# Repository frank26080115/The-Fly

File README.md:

# The-Fly

This device is a Bluetooth meeting audio recording device. It can record meetings, phone calls, or voice memos. During the recording, the user can also use this device to participate in the meeting, as it features a speaker, a earphone jack, and internal microphone.

The audio recordings are stored on a microSD card.

It features Wi-Fi connectivity so that AI can be used to transcribe and summarize the audio recordings. A local network PC can run scripts that run local AI models that performs the transcription and summarization.

## User Manuals

 * [Main Device](user-docs/user-manual-main-device.md)
 * [Wi-Fi Operations](user-docs/user-manual-wifi-operations.md)
 * [Local Server](user-docs/user-manual-local-server.md)

## Technical Breakdown

The device is a [M5Stack Core2](https://docs.m5stack.com/en/core/core2). It features a ESP32-D0WDQ6-V3 as the main microcontroller. This microcontroller features Bluetooth Classic and Wi-Fi connectivity.

There is a colour LCD screen with a capacitive touch panel, used to implement the GUI. The GUI is structured for quick usage, with shortcuts to your favorite Bluetooth host devices and the ability to instantly start a memo recording.

The Fly connects to any Bluetooth host, such as a smartphone or a laptop, using the "hands free profile", meaning it pretends to be a early 2010s era earphone and microphone, which gives it nearly universal compatibility with all host devices and all host software. No need to install any dedicated software, and it is practically impossible to detect or block.

Wi-Fi operation is implemented so the user can download and transcribe the recorded audio files. The process can be automated to any level the user desires. All the software can be completely local and private.

To improve audio quality, I've also created a daughterboard for the M5Stack Core2 that uses a SGTL5000 codec and provides a earphone jack along with a better internal mic, plus it supports inline mics on the earbuds.

(note: the original internal speaker and internal mic of the M5Stack Core2 have terrible audio quality)

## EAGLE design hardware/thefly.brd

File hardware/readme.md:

circuit designs and mechanical designs

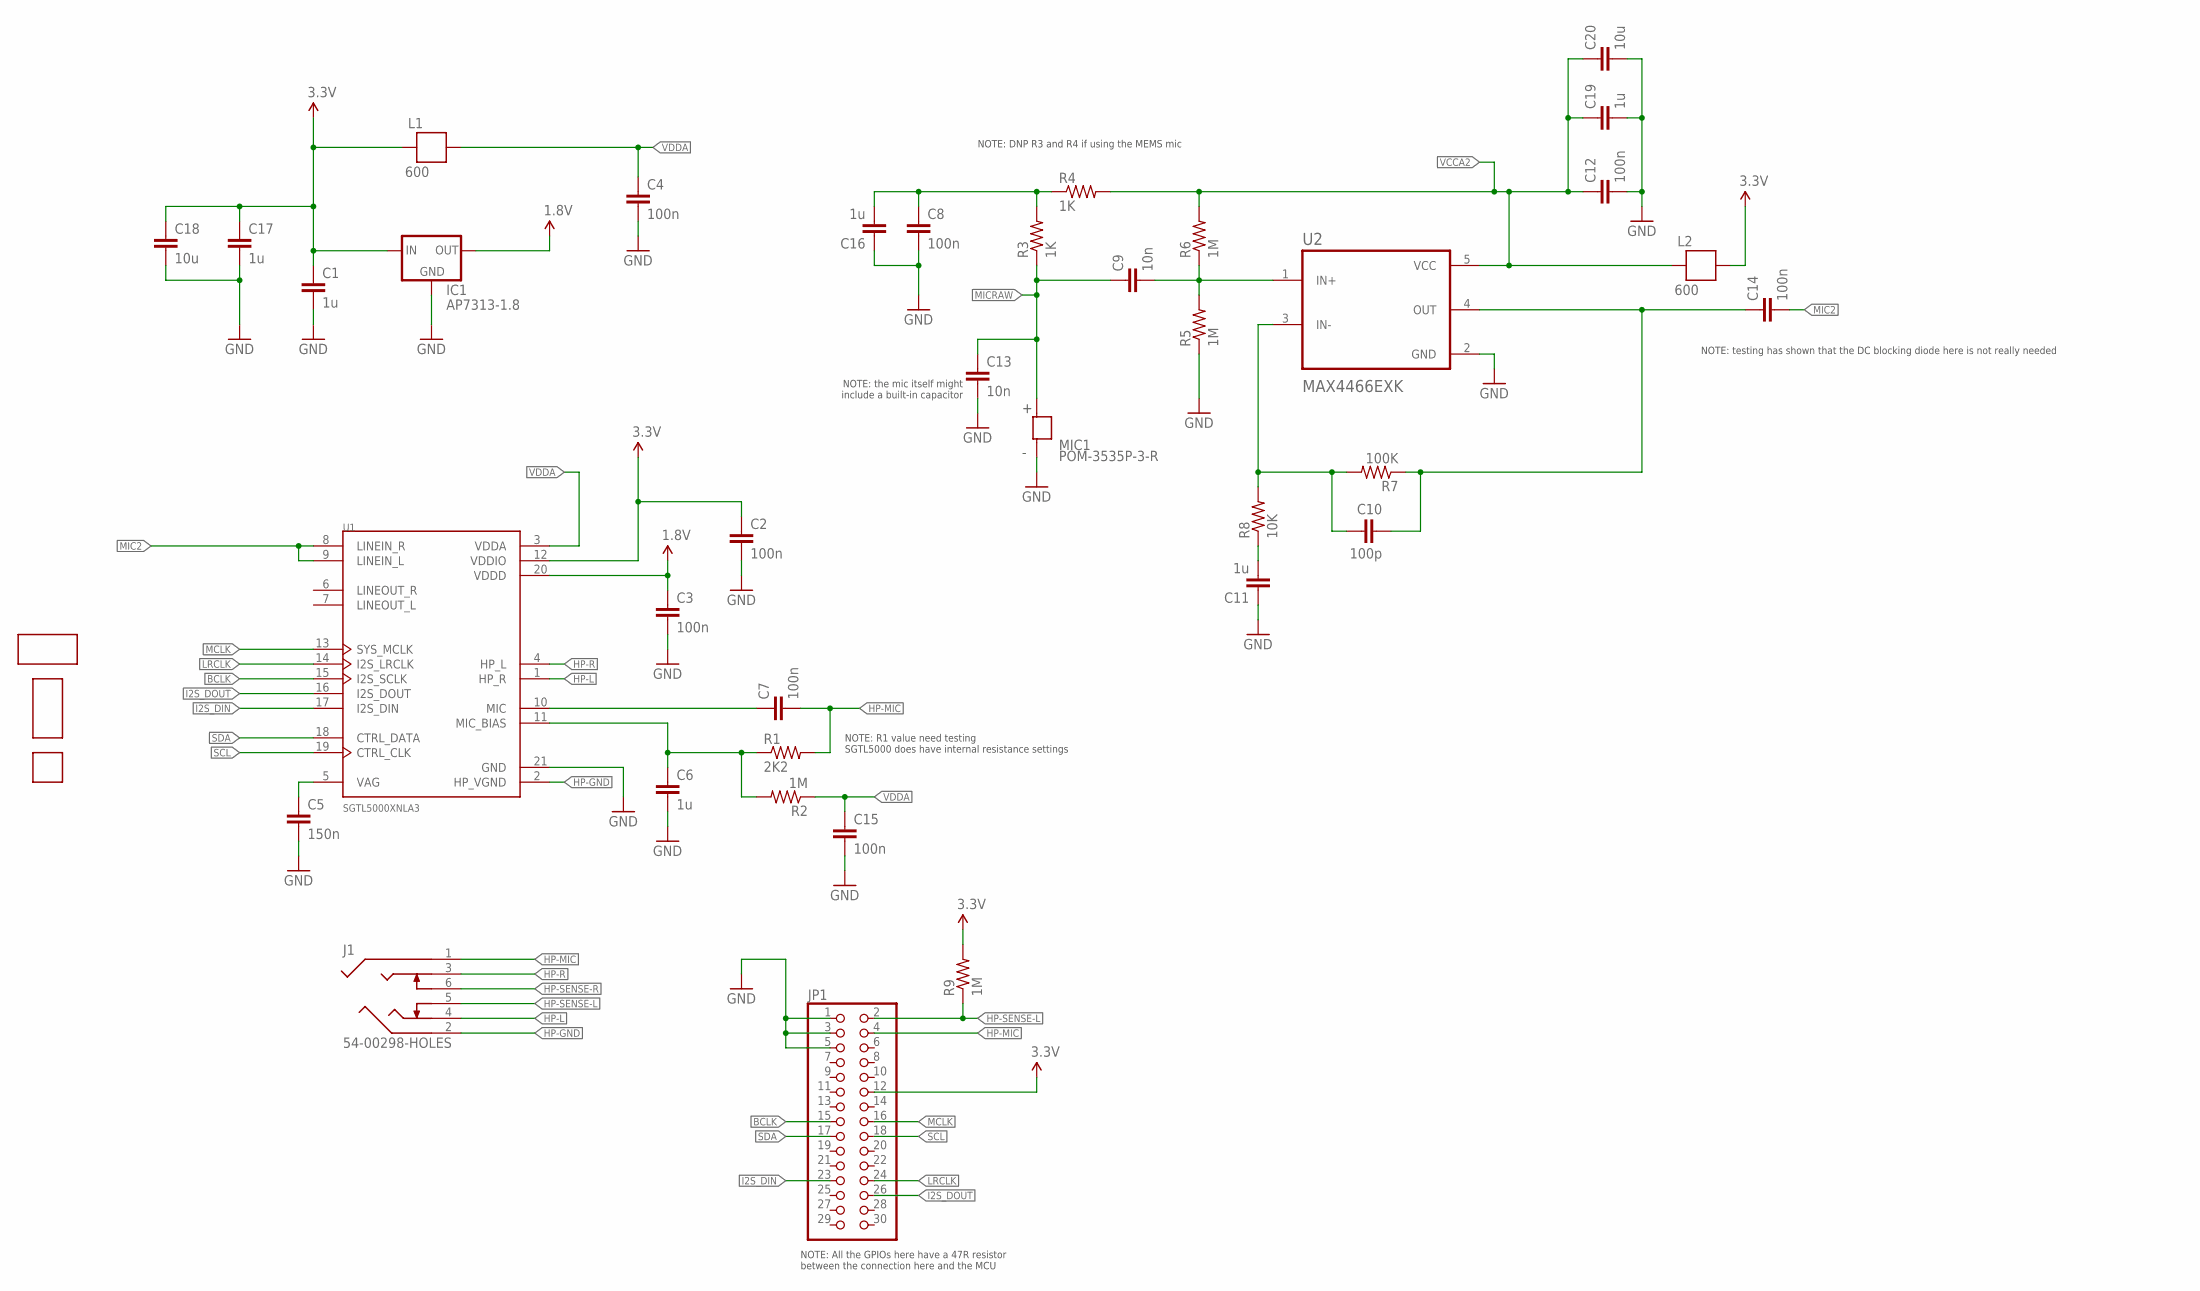
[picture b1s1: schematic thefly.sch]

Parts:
C1, C6, C11, C16, C17, C19: 1u; 0603-CAP
C2, C3, C4, C7, C8, C12, C14, C15: 100n; 0603-CAP
C5: 150n; 0603-CAP
C9, C13: 10n; 0603-CAP
C10: 100p; 0603-CAP
C18, C20: 10u; 0603-CAP
IC1: AP7313-1.8; SOT23-3
J1: 54-00298-HOLES; TENSILITY_54-00298_HOLES
JP1: PINHD-2X15-SMD-R; 2X15-SMD-R
L1, L2: 600; 0603
MIC1: POM-3535P-3-R; MIC_POM-3535P-3-R
R1: 2K2; 0603-RES
R2, R5, R6, R9: 1M; 0603-RES
R3, R4: 1K; 0603-RES
R7: 100K; 0603-RES
R8: 10K; 0603-RES
U1: SGTL5000XNLA3; QFN40P300X300X60-21N
U2: MAX4466EXK; SOT65P210X110-5N
U$1: M5STACK-CORE2-DAUGHTER
U$2: M5STACK-BATT-OUTLINE
U$5: THE-FLY-LOGO

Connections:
1.8V: C3.1, IC1.2 (OUT), U1.20 (VDDD)
3.3V: C1.1, C2.1, C17.1, C18.1, IC1.1 (IN), JP1.12, L1.2, L2.1, R9.2, U1.12 (VDDIO)
ASDASDASD: C10.2, C14.1, R7.1, U2.4 (OUT)
BCLK: JP1.15, U1.15 (I2S_SCLK)
GND: C1.2, C2.2, C3.2, C4.2, C5.2, C6.2, C8.2, C11.1, C12.2, C13.2, C15.2, C16.1, C17.2, C18.2, C19.2, C20.2, IC1.3 (GND), JP1.1, JP1.3, JP1.5, MIC1.N (-), R5.1, U1.21 (GND), U2.2 (GND)
HP-GND: J1.2, U1.2 (HP_VGND)
HP-L: J1.4, U1.1 (HP_R)
HP-MIC: C7.2, J1.1, JP1.4, R1.2
HP-R: J1.3, U1.4 (HP_L)
HP-SENSE-L: J1.5, JP1.2, R9.1
HP-SENSE-R: J1.6
I2S_DIN: JP1.23, U1.17 (I2S_DIN)
I2S_DOUT: JP1.26, U1.16 (I2S_DOUT)
LRCLK: JP1.24, U1.14 (I2S_LRCLK)
MCLK: JP1.16, U1.13 (SYS_MCLK)
MIC2: C14.2, U1.8 (LINEIN_R), U1.9 (LINEIN_L)
MICRAW: C9.1, C13.1, MIC1.P (+), R3.1
unnamed: C5.1, U1.5 (VAG)
unnamed: C6.1, R1.1, R2.2, U1.11 (MIC_BIAS)
unnamed: C7.1, U1.10 (MIC)
unnamed: C10.1, R7.2, R8.2, U2.3 (IN-)
unnamed: C11.2, R8.1
unnamed: C9.2, R5.2, R6.1, U2.1 (IN+)
unnamed: C8.1, C16.2, R3.2, R4.1
SCL: JP1.18, U1.19 (CTRL_CLK)
SDA: JP1.17, U1.18 (CTRL_DATA)
VCCA2: C12.1, C19.1, C20.1, L2.2, R4.2, R6.2, U2.5 (VCC)
VDDA: C4.1, C15.1, L1.1, R2.1, U1.3 (VDDA)

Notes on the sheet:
NOTE: All the GPIOs here have a 47R resistor between the connection here and the MCU
NOTE: DNP R3 and R4 if using the MEMS mic
NOTE: R1 value need testing SGTL5000 does have internal resistance settings
NOTE: testing has shown that the DC blocking diode here is not really needed
NOTE: the mic itself might include a built-in capacitor

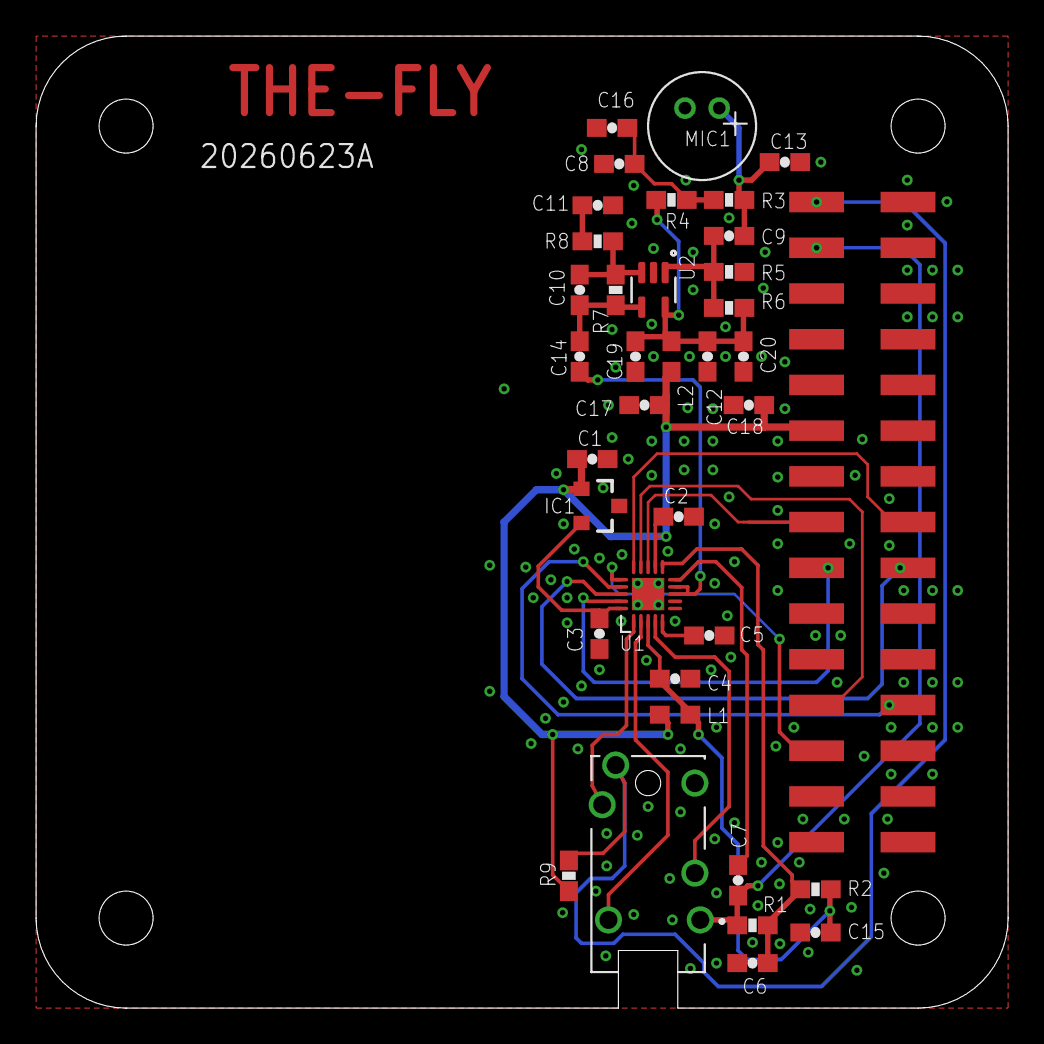
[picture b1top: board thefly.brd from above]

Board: 2 copper layers, 54.0 x 54.0 mm, 40 parts (0 on the bottom side), 27 nets.

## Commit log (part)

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2026-05-18 better build parameters
2026-05-18 test the json file loading
2026-05-18 added filepkt_src_e
2026-05-18 audio stream now embeds meta text
2026-05-19 good progress working on GUI but ran into memory problems with PNG decode
2026-05-19 iram freed up so now png drawing works because psram available
2026-05-19 cleaned up display as param
2026-05-19 fixed build errors
2026-05-19 more graphics
2026-05-19 buttons can be dimmed/dithered
2026-05-19 quick check for default phone and laptop
2026-05-19 ConnWaitingView
2026-05-19 added a scrollview
2026-05-20 massive progress with RecordingView
2026-05-20 good progress on GUI
2026-05-20 disk stats, font changes
2026-05-21 more gui work, auto bt reconnect
2026-05-21 graphics revamp normalize to 100x100 imgs
2026-05-21 build was bootlooping, got it fixed
2026-05-21 test build to try fixing dev initiated bt connection
    I made the next diagnostic change: BluetoothManager.cpp now initializes and returns closed Bluetooth state to ESP_BT_NON_CONNECTABLE / ESP_BT_NON_DISCOVERABLE, matching the old working code more clos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
    This is deliberately a test build: passive host-initiated connection while idle may not work in this version. The point is to test whether ESP32-initiated HFP starts working when HFP is initialized f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
2026-05-21 CPU frequency is the reason why it was failing to connect
2026-05-21 bt host delete, debug shown on top bar
2026-05-21 fix flickering
2026-05-21 spritedraw now supports transparency
2026-05-22 starting to add a web server
2026-05-22 ftp server works
2026-05-22 added progmem to web assets
2026-05-22 moved the ftp library to my fork
2026-05-22 ftp code organization
2026-05-22 cloud upload now includes a time nonce
2026-05-22 recording works great now, tweaked the ui
2026-05-22 minor clean up
2026-05-23 decoder script less useless warnings
2026-05-23 more sprites
2026-05-23 more security related stuff, added aegis
2026-05-23 prepping for adding NVS config store
2026-05-23 adding project default sdkconfig, it's not a good one
2026-05-23 sdkconfig changed it to a working one
2026-05-23 tested SD card with encryption
2026-05-23 some work on secured web interactions
2026-05-24 added "set_cfg" request handler
2026-05-24 more sprites, including overlays, goes along with icon rewrite
2026-05-24 work on html front-end
2026-05-24 update security and web access policies
2026-05-24 user customized icon rewrite
2026-05-24 added default salt and test password gen to aegis
2026-05-24 cleaned up usage of password in cloud, todo: add real authentication
2026-05-24 web server related major work
2026-05-24 bt connectable during memo recortding
2026-05-25 I'm checking in this state before tearing it all down
2026-05-25 major security implementation documentation change
2026-05-25 added security levels in docs, will implement later
2026-05-26 clean up for security levels
2026-05-26 new splash
2026-05-26 got rid of the temp key in frontend
2026-05-26 nvs load and save test
2026-05-26 deleted SBC stuff
2026-05-26 frontend row cloning
2026-05-26 decoder handles encrypted files
2026-05-26 removed unused views
2026-05-26 scroll view for cloud better url display
2026-05-26 attempt to make build more reliable
2026-05-26 wip on front-end interaction
2026-05-26 gfx for future security related work
2026-05-26 update security doc
2026-05-26 memory reset button on frontend
2026-05-26 password reset mechanism implementation
2026-05-26 reset memory button implementation
2026-05-26 implement the wifi ap view
2026-05-26 more text to splashview
2026-05-26 expose connected mac and cnts in ap view
2026-05-26 codex pace checker
2026-05-26 good progress on front end, organized the js files a bit, password and memory reset implemented
2026-05-26 HTTPS cloud upload
2026-05-26 mpu features enabled
2026-05-26 added codex history
2026-05-26 cloud upload progress view
2026-05-27 more codex history
2026-05-27 codex history cleanup open tabs
2026-05-27 documentation update
2026-05-27 more icons
2026-05-27 random ssid
2026-05-27 splash screen format
2026-05-27 added mdns
2026-05-27 platformio.ini removed a useless lib
2026-05-27 low level soft ap startup
2026-05-27 seem to fix the bad IP display issue
2026-05-27 serving pages over soft AP works, had a hiccup about disk space retrieval too slow tripping the wdt
2026-05-28 fixed build annoyance
2026-05-28 codex history update
2026-05-28 single name column for BT hosts
2026-05-28 ai summarization
2026-05-29 memo type file names
2026-05-29 wired up the meta text stuff for recorded files
2026-05-29 align transcription with recording meta data
2026-05-29 moved some utility funcs
2026-05-29 fixed typo
2026-05-29 fixing typo
2026-05-29 fix sprite typo
2026-05-29 code neatened, remove cloud features with a predefine
2026-05-29 more cleanup about disabling cloud
2026-05-29 some uncommon shutdown scenarios
2026-05-29 fixed crashing BT connection
2026-05-29 major progress on usability, added ntp sync
2026-05-29 ntp actually works now
2026-05-29 better error screens with rescue wifi
2026-05-29 moved progress bar into its own element
2026-05-29 fw updater polish
2026-05-30 added a decoder
2026-05-30 direct to wav file recording
2026-05-30 most recent file lister now dynamic
2026-05-30 benchmarking file listing and sorting
2026-05-30 file related sprites
2026-05-30 playback mechanism
2026-05-30 playback cosmetics
2026-05-31 transcription AI prompts
2026-05-31 bigger file list, with file type filters
2026-05-31 removed custom audio format, changed to encrypted wav
2026-05-31 pin pad
2026-05-31 encrypted playback
2026-05-31 made debug logging work again
2026-05-31 fixed encrypted recording being too short
2026-05-31 pin code backend infrastructure
2026-05-31 pin code web related implementation
2026-05-31 internal clock needs to actually care about time zone
2026-05-31 added qr code for wifi ap
2026-05-31 realigned front-end authentication method to use session key
2026-05-31 untested web decrypted download
2026-05-31 added another mock switch
2026-05-31 python script rewrite for new file format
2026-06-01 file download and decrypted downloads work now
2026-06-01 remove silence chunks
2026-06-01 added a copy of arduino-liblame
2026-06-01 liblame reconfigured
2026-06-01 more mp3 related constants
2026-06-01 preping docs for mp3 build
2026-06-01 added libhelix
2026-06-01 mp3 encode disable reservoir
2026-06-01 fixed some stuff in liblame, logging, PSRAM, null ptr exception
2026-06-01 significant work trying to get MP3 encoding to work
2026-06-01 shine encoder implemented, it
2026-06-01 mp3 playback works
2026-06-01 a lot of duplicate string comparison implementations
2026-06-01 web changes to support MP3 and encrypted MP3
2026-06-01 added mp3 support to python scripts
2026-06-02 test encryptor script handles mp3 correctly
2026-06-02 python scripts alignment, clean up and comments
2026-06-02 human code review just a bit
2026-06-02 code clean up a bit, better error dialog routing
2026-06-02 Update .clang-format
2026-06-02 clang-format
2026-06-02 update clang format scripts with ignore list
2026-06-02 neatened up AudioFileRecorder
2026-06-02 neatened up DiskStats
2026-06-02 more code neatening
2026-06-02 neater AudioManager
2026-06-02 removed liblame
2026-06-02 comments labeling modules
2026-06-02 another pass for neatening the code
2026-06-02 code neatening for the views
2026-06-02 nneaten
2026-06-02 neaten
2026-06-02 update note about reservoir bit
2026-06-02 ran clang format
2026-06-02 add the bundle for webcrypto shim
2026-06-02 file list view now use deterministic unique icon graphics
2026-06-03 refactor wifi manager
2026-06-03 clang format
2026-06-03 diagnostics, fixed a bug with speaker peak decay
2026-06-03 more clang format stuff
2026-06-03 playback error text reposition
2026-06-03 randomized file explorer buttons
2026-06-03 another splash screen
2026-06-03 boot splash disk info and timezone
2026-06-03 benchmarked mp3 encoder again with random noise
2026-06-03 benchmarked js key derivation speeds
2026-06-03 added screen fades during slow parts
2026-06-03 pins.h, tweaked FIFOs, added a test result
2026-06-03 prevent rare race condition that restarts a recording from phone
2026-06-03 mic usage now remembers speaker preference
2026-06-04 speaker peak decay rate increased
2026-06-04 haptics implemented across the board
2026-06-04 file upload now reliable
2026-06-04 mp3 playback attempt to support other formats
2026-06-04 more haptics
2026-06-04 web file delete button now async
2026-06-04 testing macro
2026-06-04 made ftp server thread safe
2026-06-04 special icon to mark special builds
2026-06-04 web file list exposes file size
2026-06-04 added potentially useful MCLK pin def
2026-06-04 WiFi now makes GUI updates slower
2026-06-05 small documentation corrections
2026-06-05 splashview timezone str shorter
2026-06-05 change door icon for wifi sta mode view
2026-06-05 add missing haptic
2026-06-05 python changed to use newer scripts
2026-06-05 elec layout progress
2026-06-05 elec layout wip
2026-06-05 changed the wifi info button icon
2026-06-05 way better time sync from browser, with timezones
2026-06-05 adding teensy library for SGTL5000
2026-06-05 external codec implementation
2026-06-05 new button graphics to indicate earbud
2026-06-05 fixed the case when writing cfg from web will wipe out the SSID being displayed
2026-06-05 fixed new i2c code from codec crashing
2026-06-06 more pcb work
2026-06-06 pcb layout wip
2026-06-06 pcb wip
2026-06-06 mock ext codec test
2026-06-06 NS4168 works on stereo, added SGTL5000 config for our I2S format
2026-06-06 update desired external codec implementation documentation
2026-06-07 progress on ext codec
2026-06-07 more mclk pin shenanigans
2026-06-08 ledc as mclk shenanigans
2026-06-08 more test notes
2026-06-11 testing to see if SGTL5000 shows up on I2C
2026-06-11 got sound out of SGTL5000 earbuds
2026-06-11 wifi soft ap now randomizes channel
2026-06-11 ext codec playback with ledc pwm as mclk
2026-06-11 volume ceiling, and went back to using software vol control
2026-06-11 update doc to reflect I2S start sequence
2026-06-11 screenshotting build
2026-06-11 screenshot now works without disturbing recording
2026-06-12 screenshot fixed
2026-06-12 user manual update
2026-06-12 splash screen says a click message
2026-06-12 more screenshot stuff
2026-06-12 ftp password change
2026-06-12 user manual documentation, python install instructions
2026-06-12 doc update
2026-06-13 fix small build errors around ftp
2026-06-13 free'ed some RAM, sec1 build crashing maybe fixed
2026-06-13 some screenshots for user manual
2026-06-14 fixed build problem about mdns ram
2026-06-14 free up even more ram
2026-06-14 time sync always available
2026-06-14 more user manual edits
2026-06-14 moved a buffer allocation function to utilfuncs
2026-06-14 dev documentation update
2026-06-15 add sync_mic_filter_for_external_codec_state
2026-06-15 layout change to add dc block on mic path
2026-06-15 lower default gains for codec
2026-06-15 user manual more pics
2026-06-15 more adjustments for mic gain
2026-06-17 mic tweaks, db scale peak display
2026-06-17 mic spectrum test
2026-06-18 more mic tuning
2026-06-18 implemented notch filter for mic noise problem
2026-06-23 pcb layout removed agnd, more caps
2026-06-23 update docs with photos
2026-06-23 pamphlet
2026-06-24 pcb layout change
2026-06-24 added dummy cloud dialog
2026-06-24 removed security level display for 0 level
2026-06-24 fixed frozen error dialog
2026-06-24 update version
2026-06-24 reenable mp3
2026-06-24 test to debug bad PCB solder joint
2026-06-25 enforce ext codec
2026-06-25 scrollview fix loop bug when deleting and leaving only one item
2026-06-25 master hardware test
2026-06-25 fixed uninitialized RTC showing weird number
2026-06-25 fix single item loop after delete
2026-06-25 fixed delete button needing 3 presses
2026-06-25 ZZZ display for pwr key
2026-06-26 security build tools
2026-06-26 more fixes for missing py modules during secure fw build
2026-06-26 build_security now uses internal code for key generation
2026-06-26 untracked version.c since it's auto generated
2026-06-27 anti-rollback
2026-06-27 mic gain manager has a max gain setting
2026-06-27 weak mic now switches to internal mic
